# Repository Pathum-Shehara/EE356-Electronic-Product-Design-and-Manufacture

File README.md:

# EE356-Electronic-Product-Design-and-Manufacture
Color Sensing Device for Visually Impaired Person

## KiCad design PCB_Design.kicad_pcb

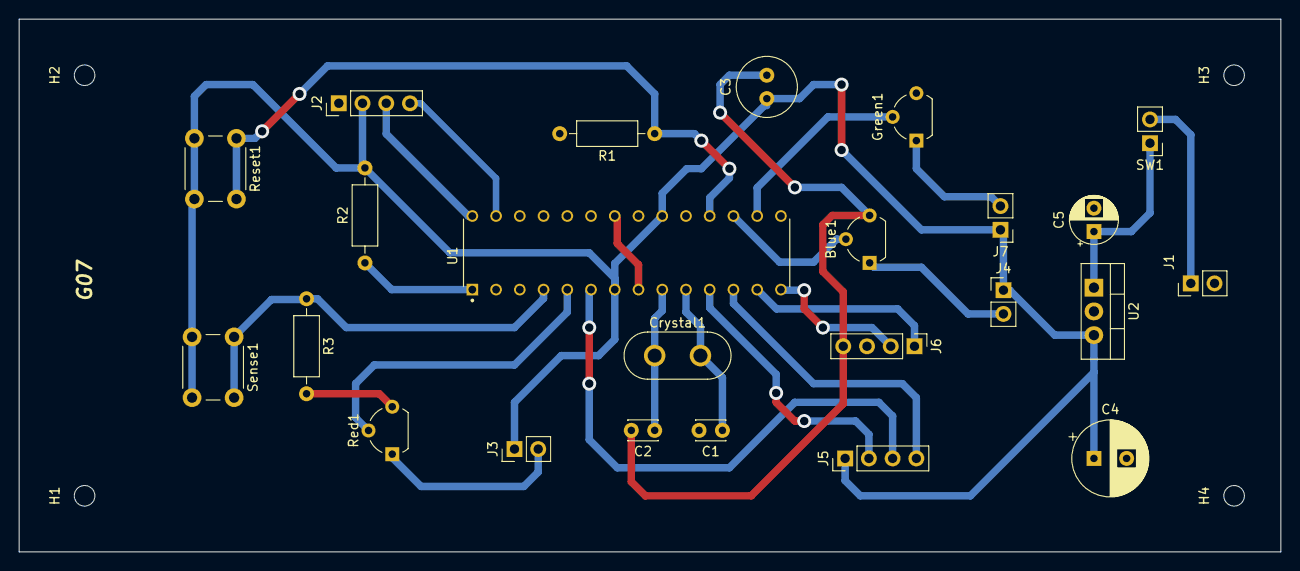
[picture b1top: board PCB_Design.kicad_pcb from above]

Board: 2 copper layers, 135.0 x 57.0 mm, 28 parts (0 on the bottom side), 22 nets.

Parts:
Blue1: BC337; TO-92L_Wide
C1, C2: 22pF; C_Disc_D3.0mm_W2.0mm_P2.50mm
C3: 10uF; C_Radial_D6.3mm_H5.0mm_P2.50mm
C4: 0.1uF; CP_Radial_D8.0mm_P3.50mm
C5: 0.22uF; CP_Radial_D5.0mm_P2.50mm
Crystal1: 16MHz; Crystal_HC50_Vertical
Green1: BC337; TO-92L_Wide
H1, H2, H3, H4: MountingHole; MountingHole_2.2mm_M2
J1: Power In; PinHeader_1x02_P2.54mm_Vertical
J2: OLED; PinHeader_1x04_P2.54mm_Vertical
J3: Red Vibrator; PinHeader_1x02_P2.54mm_Vertical
J4: Blue Vibrator; PinHeader_1x02_P2.54mm_Vertical
J5: TCS3200 Side 1; PinHeader_1x04_P2.54mm_Vertical
J6: TCS3200 Side 2; PinHeader_1x04_P2.54mm_Vertical
J7: Green Vibrator; PinHeader_1x02_P2.54mm_Vertical
R1, R3: 1k; R_Axial_DIN0207_L6.3mm_D2.5mm_P10.16mm_Horizontal
R2: 10k; R_Axial_DIN0207_L6.3mm_D2.5mm_P10.16mm_Horizontal
Red1: BC337; TO-92L_Wide
Reset1: SW_Push; SW_PUSH_6mm
SW1: SW_DPST_x2; PinHeader_1x02_P2.54mm_Vertical
Sense1: SW_Push; SW_PUSH_6mm
U1: ATmega328P-PU; DIP787W46P254L3467H508Q28
U2: LM7805_TO220; TO-220-3_Vertical

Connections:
A4: J2.4, U1.27 (PC4)
A5: J2.3, U1.28 (PC5)
D2: R3.1, Sense1.1, U1.4 (PD2)
D3: Red1.2 (B), U1.5 (PD3)
D4: J5.3, U1.6 (PD4)
D5: J5.2, U1.11 (PD5)
D6: J5.4, U1.12 (PD6)
D7: J6.1, U1.13 (PD7)
D8: J6.2, U1.14 (PB0)
D10: Green1.2 (B), U1.16 (PB2)
D11: Blue1.2 (B), U1.17 (PB3)
D12: R1.1, Reset1.1, U1.18 (PB4)
GND: Blue1.3 (E), C1.2, C2.2, C3.2, C4.2, C5.2, Green1.3 (E), J1.2, J2.1, J6.4, R1.2, R3.2, Red1.3 (E), U1.8 (GND), U1.22 (GND), U2.2 (GND)
unnamed: Blue1.1 (C), J4.2
unnamed: C1.1, Crystal1.2, U1.10 (XTAL2/PB7)
unnamed: C2.1, Crystal1.1, U1.9 (XTAL1/PB6)
unnamed: C5.1, SW1.1 (A), U2.1 (VI)
unnamed: Green1.1 (C), J7.2
unnamed: J1.1, SW1.2 (B)
unnamed: J3.2, Red1.1 (C)
unnamed: R2.1, U1.1 (~RESET/PC6)
VCC: C3.1, C4.1, J2.2, J3.1, J4.1, J5.1, J7.1, R2.2, Reset1.2, Sense1.2, U1.7 (VCC), U1.20 (AVCC), U2.3 (VO)
